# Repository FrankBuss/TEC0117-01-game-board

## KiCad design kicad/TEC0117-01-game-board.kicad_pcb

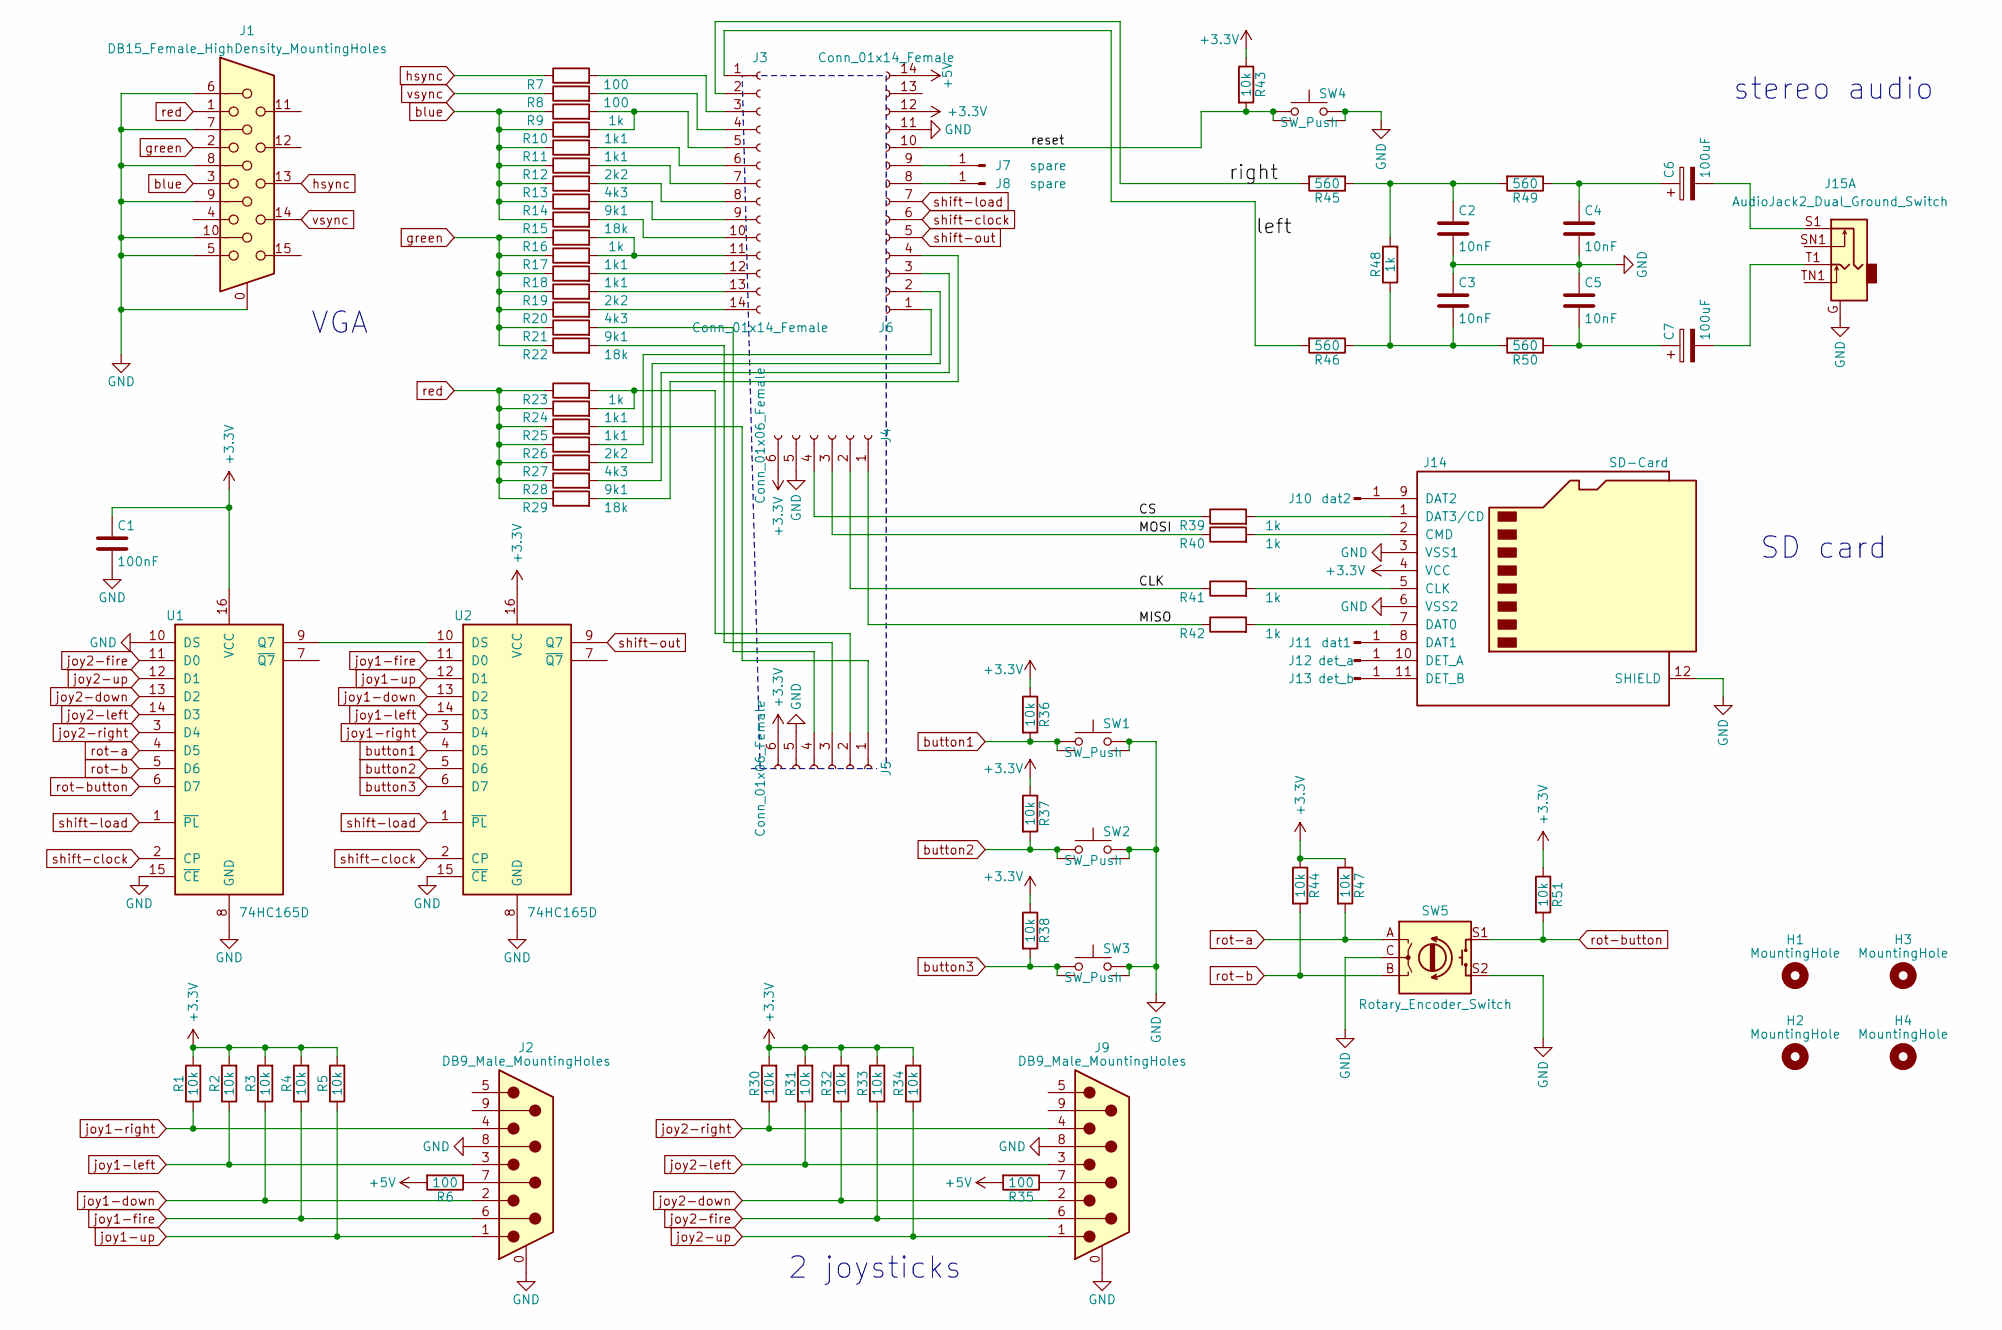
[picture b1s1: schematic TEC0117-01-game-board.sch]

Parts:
C1: 100nF; C_0805_2012Metric
C2, C3, C4, C5: 10nF; C_0805_2012Metric
C6, C7: 100uF; C_Radial_D8.0mm_H7.0mm_P3.50mm
H1, H2, H3, H4: MountingHole; MountingHole_3.2mm_M3
J1: DB15_Female_HighDensity_MountingHoles; DSUB-15-HD_Female_Horizontal_P2.29x1.98mm_EdgePinOffset8.35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
J2, J9: DB9_Male_MountingHoles; DSUB-9_Male_Horizontal_P2.77x2.84mm_EdgePinOffset4.94mm_Hou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
J3, J6: Conn_01x14_Female; PinSocket_1x14_P2.54mm_Vertical
J4, J5: Conn_01x06_Female; PinSocket_1x06_P2.54mm_Vertical
J7, J8: spare; PinSocket_1x01_P2.54mm_Vertical
J10: dat2; PinSocket_1x01_P2.54mm_Vertical
J11: dat1; PinSocket_1x01_P2.54mm_Vertical
J12: det_a; PinSocket_1x01_P2.54mm_Vertical
J13: det_b; PinSocket_1x01_P2.54mm_Vertical
J14: SD-Card; sd-card
J15: AudioJack2_Dual_Ground_Switch; ft6320
R1, R2, R3, R4, R5, R30, R31, R32, R33, R34, R36, R37, R38, R43, R44, R47, R51: 10k; R_0805_2012Metric
R6, R7, R8, R35: 100; R_0805_2012Metric
R9, R16, R23, R39, R40, R41, R42, R48: 1k; R_0805_2012Metric
R10, R11, R17, R18, R24, R25: 1k1; R_0805_2012Metric
R12, R19, R26: 2k2; R_0805_2012Metric
R13, R20, R27: 4k3; R_0805_2012Metric
R14, R21, R28: 9k1; R_0805_2012Metric
R15, R22, R29: 18k; R_0805_2012Metric
R45, R46, R49, R50: 560; R_0805_2012Metric
SW1, SW2, SW3, SW4: SW_Push; B3F-through-hole
SW5: Rotary_Encoder_Switch; RotaryEncoder_Alps_EC11E-Switch_Vertical_H20mm
U1, U2: 74HC165D; SOIC-16_3.9x9.9mm_P1.27mm

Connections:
+3V3: C1.1, J4.6, J5.6, J6.12, J14.4 (VCC), R1.2, R2.2, R3.2, R4.2, R5.2, R30.2, R31.2, R32.2, R33.2, R34.2, R36.1, R37.1, R38.1, R43.1, R44.1, R47.1, R51.1, U1.16 (VCC), U2.16 (VCC)
+5V: J6.14, R6.2, R35.2
/CLK: J4.2, R41.1
/CS: J4.4, R39.1
/MISO: J4.1, R42.1
/MOSI: J4.3, R40.1
/left: J3.1, R46.2
/reset: J6.10, R43.2, SW4.1, SW4.2
/right: J3.2, R45.2
GND: C1.2, C2.2, C3.1, C4.2, C5.1, J1.0, J1.5, J1.6, J1.7, J1.8, J1.9, J1.10, J2.0 (PAD), J2.8, J4.5, J5.5, J6.11, J9.0 (PAD), J9.8, J14.3 (VSS1), J14.6 (VSS2), J14.12 (SHIELD), J15.G, SW1.3, SW1.4, SW2.3, SW2.4, SW3.3, SW3.4, SW4.3, SW4.4, SW5.C, SW5.S2, U1.8 (GND), U1.10 (DS), U1.15 (~CE), U2.8 (GND), U2.15 (~CE)
unnamed: C2.1, R45.1, R48.2, R49.2
unnamed: C3.2, R46.1, R48.1, R50.2
unnamed: C4.1, C6.1, R49.1
unnamed: C5.2, C7.1, R50.1
unnamed: C6.2, J15.S1
unnamed: C7.2, J15.T1
unnamed: J2.7, R6.1
unnamed: J3.3, R7.2
unnamed: J3.4, R8.2
unnamed: J3.5, R9.2, R10.2
unnamed: J3.6, R11.2
unnamed: J3.7, R12.2
unnamed: J3.8, R13.2
unnamed: J3.9, R14.2
unnamed: J3.10, R15.2
unnamed: J3.11, R16.2, R17.2
unnamed: J3.12, R18.2
unnamed: J3.13, R19.2
unnamed: J3.14, R20.2
unnamed: J5.1, R25.2
unnamed: J5.2, R23.2, R24.2
unnamed: J5.3, R22.2
unnamed: J5.4, R21.2
unnamed: J6.1, R26.2
unnamed: J6.2, R27.2
unnamed: J6.3, R28.2
unnamed: J6.4, R29.2
unnamed: J6.8, J8.1
unnamed: J6.9, J7.1
unnamed: J9.7, R35.1
unnamed: J10.1, J14.9 (DAT2)
unnamed: J11.1, J14.8 (DAT1)
unnamed: J12.1, J14.10 (DET_A)
unnamed: J13.1, J14.11 (DET_B)
unnamed: J14.1 (DAT3/CD), R39.2
unnamed: J14.2 (CMD), R40.2
unnamed: J14.5 (CLK), R41.2
unnamed: J14.7 (DAT0), R42.2
unnamed: U1.9 (Q7), U2.10 (DS)
blue: J1.3, R9.1, R10.1, R11.1, R12.1, R13.1, R14.1, R15.1
button1: R36.2, SW1.1, SW1.2, U2.4 (D5)
button2: R37.2, SW2.1, SW2.2, U2.5 (D6)
button3: R38.2, SW3.1, SW3.2, U2.6 (D7)
green: J1.2, R16.1, R17.1, R18.1, R19.1, R20.1, R21.1, R22.1
hsync: J1.13, R7.1
joy1-down: J2.2, R3.1, U2.13 (D2)
joy1-fire: J2.6, R4.1, U2.11 (D0)
joy1-left: J2.3, R2.1, U2.14 (D3)
joy1-right: J2.4, R1.1, U2.3 (D4)
joy1-up: J2.1, R5.1, U2.12 (D1)
joy2-down: J9.2, R32.1, U1.13 (D2)
joy2-fire: J9.6, R33.1, U1.11 (D0)
joy2-left: J9.3, R31.1, U1.14 (D3)
joy2-right: J9.4, R30.1, U1.3 (D4)
joy2-up: J9.1, R34.1, U1.12 (D1)
red: J1.1, R23.1, R24.1, R25.1, R26.1, R27.1, R28.1, R29.1
rot-a: R47.2, SW5.A, U1.4 (D5)
rot-b: R44.2, SW5.B, U1.5 (D6)
rot-button: R51.2, SW5.S1, U1.6 (D7)
shift-clock: J6.6, U1.2 (CP), U2.2 (CP)
shift-load: J6.7, U1.1 (~PL), U2.1 (~PL)
shift-out: J6.5, U2.9 (Q7)
vsync: J1.14, R8.1

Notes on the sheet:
VGA
2 joysticks
stereo audio
SD card

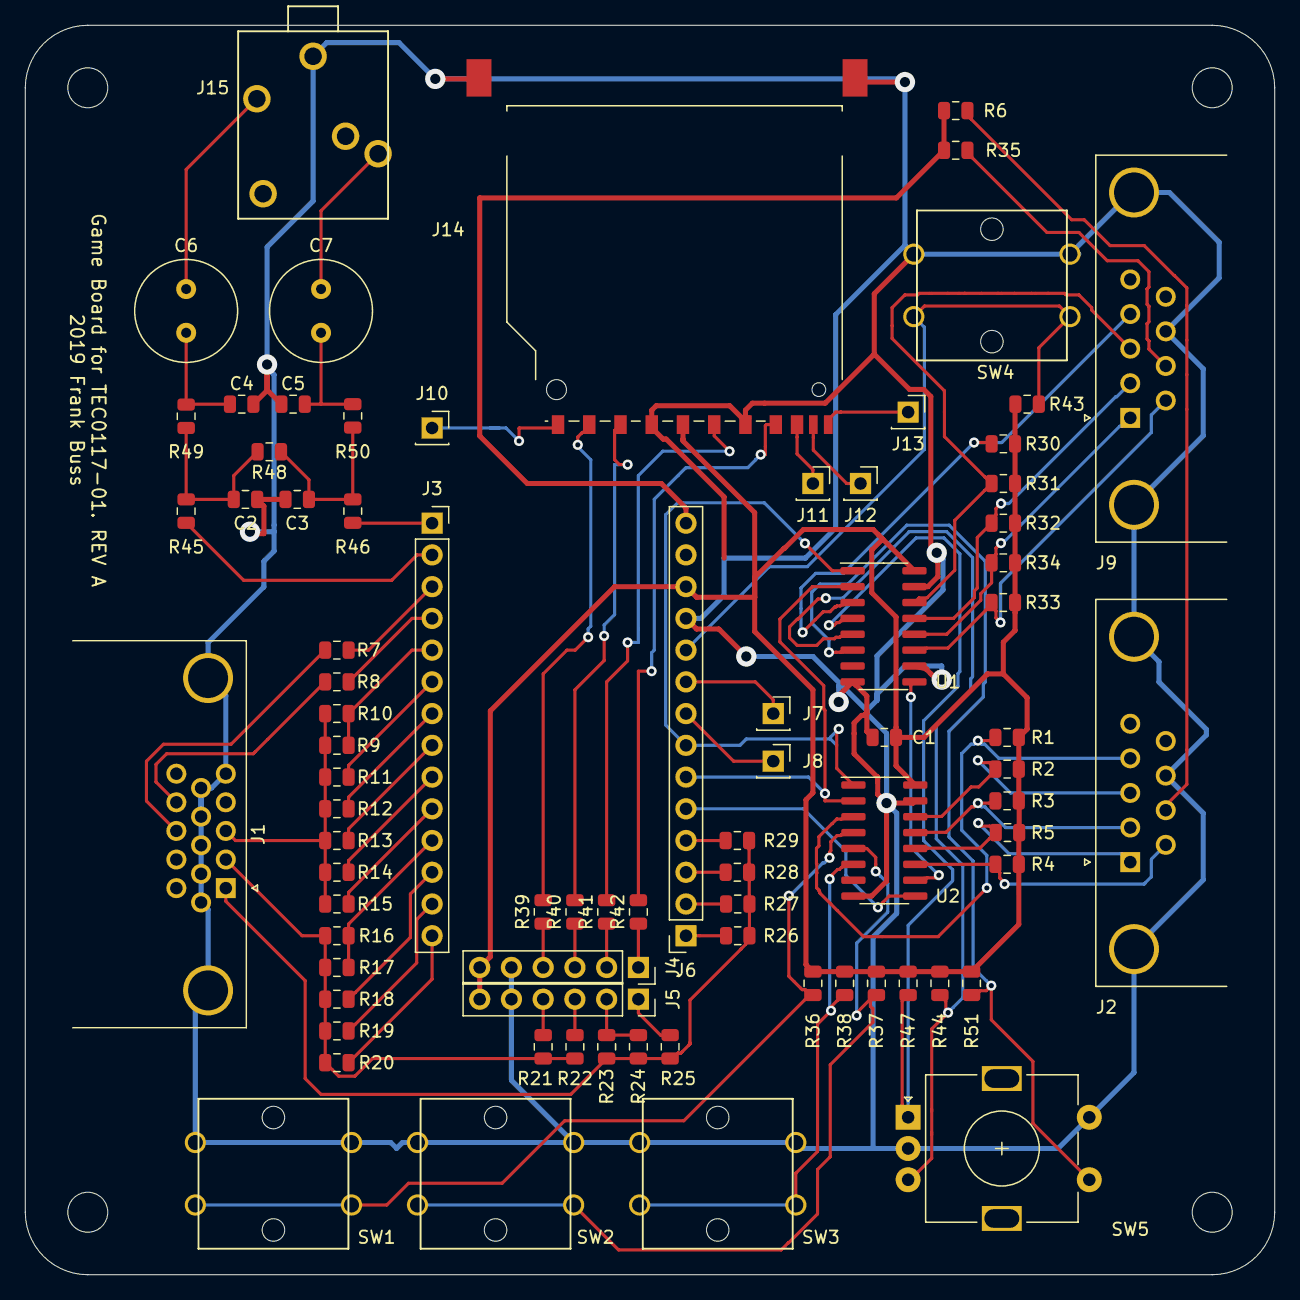
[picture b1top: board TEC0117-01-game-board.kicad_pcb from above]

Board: 2 copper layers, 100.0 x 100.0 mm, 84 parts (0 on the bottom side), 73 nets.
